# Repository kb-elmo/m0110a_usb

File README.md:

# M0110a USB
[![CC BY-NC-SA 4.0][cc-by-nc-sa-shield]][cc-by-nc-sa]

## This project is completed and will not get updated anymore.

### QMK compatible drop-in replacement PCB for the Apple M0110a
The PCB is built entirely with THT parts to keep a somewhat "vintage" look to it and it uses the fullsize 40-pin DIP package ATmega32A.
The controller is placed in the exact same location as the one on the original PCB meaning that it can be accessed through the plate cutout under the spacebar.

The board is now fully tested and works absolutely perfect. Firmware and a guide on how to flash the bootloader and firmware will be added soon.

### Partslist
 |Count|Part|
 |-|-|
 |1|ATmega32A 40 pin DIP (32L works too)|
 |1|40 pin DIP socket (optional but highly recommended)|
 |1|2x3 pin header 2.54mm (for ISP flashing)|
 |1|3mm LED (any color should work)|
 |1|JST PH 2mm 4pin connector + cable|
 |1|mini usb breakout board|
 |1|500 mA polyfuse|
 |2|6mm momentary push buttons|
 |1|16 MHz quarz crystal|
 |1|4.7 uF electrolytic capacitor|
 |2|100 nF ceramic disk capacitor|
 |2|22 pF ceramic disk capacitor|
 |1|10 kΩ resistor|
 |2|68 Ω resistor|
 |2|1.5 kΩ resistor|
 |2|3.6 V zener diode (DO-35 BZX55C3V6)|
 |78|universal switching diode (DO-35 1N4148)|

#### Some pictures of the first finished PCB

This work is licensed under a
[Creative Commons Attribution-NonCommercial-ShareAlike 4.0 International License][cc-by-nc-sa].

[![CC BY-NC-SA 4.0][cc-by-nc-sa-image]][cc-by-nc-sa]

[cc-by-nc-sa]: http://creativecommons.org/licenses/by-nc-sa/4.0/
[cc-by-nc-sa-image]: https://licensebuttons.net/l/by-nc-sa/4.0/88x31.png
[cc-by-nc-sa-shield]: https://img.shields.io/badge/License-CC%20BY--NC--SA%204.0-lightgrey.svg

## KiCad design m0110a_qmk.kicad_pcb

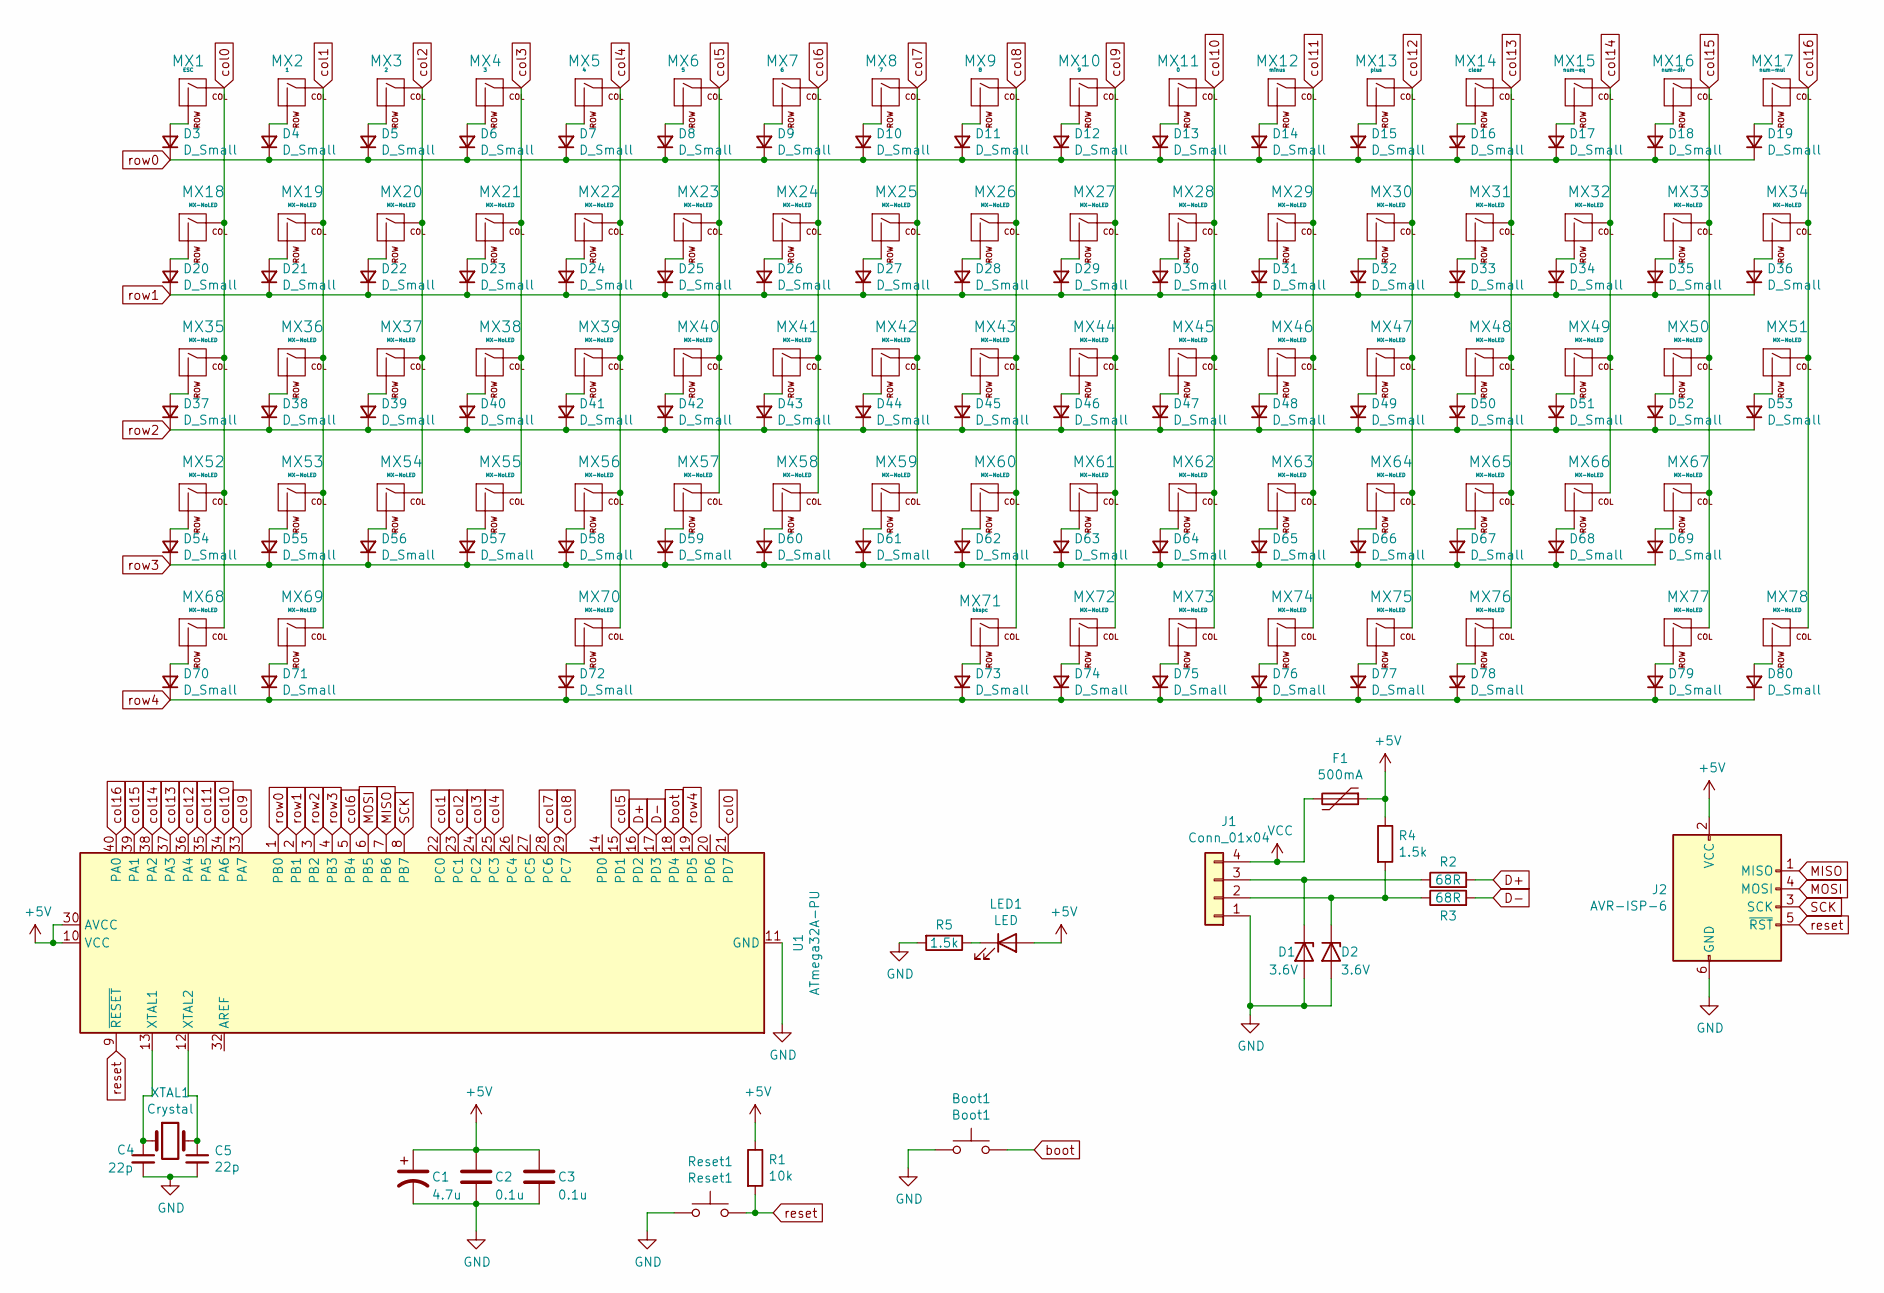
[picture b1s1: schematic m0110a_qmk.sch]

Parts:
Boot1: Boot1; SW_PUSH_6mm
C1: 4.7u; CP_Radial_D5.0mm_P2.50mm
C2, C3: 0.1u; C_Disc_D3.0mm_W2.0mm_P2.50mm
C4, C5: 22p; C_Disc_D6.0mm_W2.5mm_P5.00mm
D1, D2: 3.6V; D_DO-35_SOD27_P7.62mm_Horizontal
D3, D4, D5, D6, D7, D8, D9, D10, D11, D12, D13, D14, D15, D16, D17, D18, D19, D20, D21, D22, D23, D24, D25, D26, D27, D28, D29, D30, D31, D32, D33, D34, D35, D36, D37, D38, D39, D40, D41, D42, D43, D44, D45, D46, D47, D48, D49, D50, D51, D52, D53, D54, D55, D56, D57, D58, D59, D60, D61, D62, D63, D64, D65, D66, D67, D68, D69, D70, D71, D72, D73, D74, D75, D76, D77, D78, D79, D80: D_Small; D_DO-35_SOD27_P7.62mm_Horizontal
F1: 500mA; Fuse_Littelfuse_395Series
J1: Conn_01x04; JST_PH_S4B-PH-K_1x04_P2.00mm_Horizontal
J2: AVR-ISP-6; PinHeader_2x03_P2.54mm_Horizontal
LED1: LED; LED_D3.0mm
MX1: ESC; alps_skcc
MX2: 1; alps_skcc
MX3: 2; alps_skcc
MX4: 3; alps_skcc
MX5: 4; alps_skcc
MX6: 5; alps_skcc
MX7: 6; alps_skcc
MX8: 7; alps_skcc
MX9: 8; alps_skcc
MX10: 9; alps_skcc
MX11: 0; alps_skcc
MX12: minus; alps_skcc
MX13: plus; alps_skcc
MX14: clear; alps_skcc
MX15: num-eq; alps_skcc
MX16: num-div; alps_skcc
MX17: num-mul; alps_skcc
MX18, MX19, MX20, MX21, MX22, MX23, MX24, MX25, MX26, MX27, MX28, MX29, MX30, MX31, MX32, MX33, MX34, MX35, MX36, MX37, MX38, MX39, MX40, MX41, MX42, MX43, MX44, MX45, MX46, MX47, MX48, MX49, MX50, MX51, MX52, MX53, MX54, MX55, MX56, MX57, MX58, MX59, MX60, MX61, MX62, MX63, MX64, MX65, MX66, MX67, MX68, MX69, MX70, MX72, MX73, MX74, MX75, MX76, MX77, MX78: MX-NoLED; alps_skcc
MX71: bkspc; alps_skcc
R1: 10k; R_Axial_DIN0207_L6.3mm_D2.5mm_P10.16mm_Horizontal
R2, R3: 68R; R_Axial_DIN0207_L6.3mm_D2.5mm_P10.16mm_Horizontal
R4, R5: 1.5k; R_Axial_DIN0207_L6.3mm_D2.5mm_P10.16mm_Horizontal
Reset1: Reset1; SW_PUSH_6mm
U1: ATmega32A-PU; DIP-40_W15.24mm_Socket
XTAL1: Crystal; Crystal_HC49-4H_Vertical

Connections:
+5V: C1.1, C2.1, C3.1, F1.1, J2.2 (VCC), LED1.2 (A), R1.1, R4.1, U1.10 (VCC), U1.30 (AVCC)
D+: R2.2, U1.16 (PD2)
D-: R3.2, U1.17 (PD3)
GND: Boot1.1, C1.2, C2.2, C3.2, C4.2, C5.2, D1.2 (A), D2.2 (A), J1.1, J2.6 (GND), R5.2, Reset1.1, U1.11 (GND), U1.31 (GND)
MISO: J2.1 (MISO), U1.7 (PB6)
MOSI: J2.4 (MOSI), U1.6 (PB5)
unnamed: C4.1, U1.13 (XTAL1), XTAL1.1
unnamed: C5.1, U1.12 (XTAL2), XTAL1.2
unnamed: D1.1 (K), J1.3, R2.1
unnamed: D2.1 (K), J1.2, R3.1, R4.2
unnamed: D3.2 (A), MX1.2 (ROW)
unnamed: D4.2 (A), MX2.2 (ROW)
unnamed: D5.2 (A), MX3.2 (ROW)
unnamed: D6.2 (A), MX4.2 (ROW)
unnamed: D7.2 (A), MX5.2 (ROW)
unnamed: D8.2 (A), MX6.2 (ROW)
unnamed: D9.2 (A), MX7.2 (ROW)
unnamed: D10.2 (A), MX8.2 (ROW)
unnamed: D11.2 (A), MX9.2 (ROW)
unnamed: D12.2 (A), MX10.2 (ROW)
unnamed: D13.2 (A), MX11.2 (ROW)
unnamed: D14.2 (A), MX12.2 (ROW)
unnamed: D15.2 (A), MX13.2 (ROW)
unnamed: D16.2 (A), MX14.2 (ROW)
unnamed: D17.2 (A), MX15.2 (ROW)
unnamed: D18.2 (A), MX16.2 (ROW)
unnamed: D19.2 (A), MX17.2 (ROW)
unnamed: D20.2 (A), MX18.2 (ROW)
unnamed: D21.2 (A), MX19.2 (ROW)
unnamed: D22.2 (A), MX20.2 (ROW)
unnamed: D23.2 (A), MX21.2 (ROW)
unnamed: D24.2 (A), MX22.2 (ROW)
unnamed: D25.2 (A), MX23.2 (ROW)
unnamed: D26.2 (A), MX24.2 (ROW)
unnamed: D27.2 (A), MX25.2 (ROW)
unnamed: D28.2 (A), MX26.2 (ROW)
unnamed: D29.2 (A), MX27.2 (ROW)
unnamed: D30.2 (A), MX28.2 (ROW)
unnamed: D31.2 (A), MX29.2 (ROW)
unnamed: D32.2 (A), MX30.2 (ROW)
unnamed: D33.2 (A), MX31.2 (ROW)
unnamed: D34.2 (A), MX32.2 (ROW)
unnamed: D35.2 (A), MX33.2 (ROW)
unnamed: D36.2 (A), MX34.2 (ROW)
unnamed: D37.2 (A), MX35.2 (ROW)
unnamed: D38.2 (A), MX36.2 (ROW)
unnamed: D39.2 (A), MX37.2 (ROW)
unnamed: D40.2 (A), MX38.2 (ROW)
unnamed: D41.2 (A), MX39.2 (ROW)
unnamed: D42.2 (A), MX40.2 (ROW)
unnamed: D43.2 (A), MX41.2 (ROW)
unnamed: D44.2 (A), MX42.2 (ROW)
unnamed: D45.2 (A), MX43.2 (ROW)
unnamed: D46.2 (A), MX44.2 (ROW)
unnamed: D47.2 (A), MX45.2 (ROW)
unnamed: D48.2 (A), MX46.2 (ROW)
unnamed: D49.2 (A), MX47.2 (ROW)
unnamed: D50.2 (A), MX48.2 (ROW)
unnamed: D51.2 (A), MX49.2 (ROW)
unnamed: D52.2 (A), MX50.2 (ROW)
unnamed: D53.2 (A), MX51.2 (ROW)
unnamed: D54.2 (A), MX52.2 (ROW)
unnamed: D55.2 (A), MX53.2 (ROW)
unnamed: D56.2 (A), MX54.2 (ROW)
unnamed: D57.2 (A), MX55.2 (ROW)
unnamed: D58.2 (A), MX56.2 (ROW)
unnamed: D59.2 (A), MX57.2 (ROW)
unnamed: D60.2 (A), MX58.2 (ROW)
unnamed: D61.2 (A), MX59.2 (ROW)
unnamed: D62.2 (A), MX60.2 (ROW)
unnamed: D63.2 (A), MX61.2 (ROW)
unnamed: D64.2 (A), MX62.2 (ROW)
unnamed: D65.2 (A), MX63.2 (ROW)
unnamed: D66.2 (A), MX64.2 (ROW)
unnamed: D67.2 (A), MX65.2 (ROW)
unnamed: D68.2 (A), MX66.2 (ROW)
unnamed: D69.2 (A), MX67.2 (ROW)
unnamed: D70.2 (A), MX68.2 (ROW)
unnamed: D71.2 (A), MX69.2 (ROW)
unnamed: D72.2 (A), MX70.2 (ROW)
unnamed: D73.2 (A), MX71.2 (ROW)
unnamed: D74.2 (A), MX72.2 (ROW)
unnamed: D75.2 (A), MX73.2 (ROW)
unnamed: D76.2 (A), MX74.2 (ROW)
unnamed: D77.2 (A), MX75.2 (ROW)
unnamed: D78.2 (A), MX76.2 (ROW)
unnamed: D79.2 (A), MX77.2 (ROW)
unnamed: D80.2 (A), MX78.2 (ROW)
unnamed: LED1.1 (K), R5.1
SCK: J2.3 (SCK), U1.8 (PB7)
VCC: F1.2, J1.4
boot: Boot1.2, U1.18 (PD4)
col0: MX1.1 (COL), MX18.1 (COL), MX35.1 (COL), MX52.1 (COL), MX68.1 (COL), U1.21 (PD7)
col1: MX2.1 (COL), MX19.1 (COL), MX36.1 (COL), MX53.1 (COL), MX69.1 (COL), U1.22 (PC0)
col2: MX3.1 (COL), MX20.1 (COL), MX37.1 (COL), MX54.1 (COL), U1.23 (PC1)
col3: MX4.1 (COL), MX21.1 (COL), MX38.1 (COL), MX55.1 (COL), U1.24 (PC2)
col4: MX5.1 (COL), MX22.1 (COL), MX39.1 (COL), MX56.1 (COL), MX70.1 (COL), U1.25 (PC3)
col5: MX6.1 (COL), MX23.1 (COL), MX40.1 (COL), MX57.1 (COL), U1.15 (PD1)
col6: MX7.1 (COL), MX24.1 (COL), MX41.1 (COL), MX58.1 (COL), U1.5 (PB4)
col7: MX8.1 (COL), MX25.1 (COL), MX42.1 (COL), MX59.1 (COL), U1.28 (PC6)
col8: MX9.1 (COL), MX26.1 (COL), MX43.1 (COL), MX60.1 (COL), MX71.1 (COL), U1.29 (PC7)
col9: MX10.1 (COL), MX27.1 (COL), MX44.1 (COL), MX61.1 (COL), MX72.1 (COL), U1.33 (PA7)
col10: MX11.1 (COL), MX28.1 (COL), MX45.1 (COL), MX62.1 (COL), MX73.1 (COL), U1.34 (PA6)
col11: MX12.1 (COL), MX29.1 (COL), MX46.1 (COL), MX63.1 (COL), MX74.1 (COL), U1.35 (PA5)
col12: MX13.1 (COL), MX30.1 (COL), MX47.1 (COL), MX64.1 (COL), MX75.1 (COL), U1.36 (PA4)
col13: MX14.1 (COL), MX31.1 (COL), MX48.1 (COL), MX65.1 (COL), MX76.1 (COL), U1.37 (PA3)
col14: MX15.1 (COL), MX32.1 (COL), MX49.1 (COL), MX66.1 (COL), U1.38 (PA2)
col15: MX16.1 (COL), MX33.1 (COL), MX50.1 (COL), MX67.1 (COL), MX77.1 (COL), U1.39 (PA1)
col16: MX17.1 (COL), MX34.1 (COL), MX51.1 (COL), MX78.1 (COL), U1.40 (PA0)
reset: J2.5 (~RST), R1.2, Reset1.2, U1.9 (~RESET)
row0: D3.1 (K), D4.1 (K), D5.1 (K), D6.1 (K), D7.1 (K), D8.1 (K), D9.1 (K), D10.1 (K), D11.1 (K), D12.1 (K), D13.1 (K), D14.1 (K), D15.1 (K), D16.1 (K), D17.1 (K), D18.1 (K), D19.1 (K), U1.1 (PB0)
row1: D20.1 (K), D21.1 (K), D22.1 (K), D23.1 (K), D24.1 (K), D25.1 (K), D26.1 (K), D27.1 (K), D28.1 (K), D29.1 (K), D30.1 (K), D31.1 (K), D32.1 (K), D33.1 (K), D34.1 (K), D35.1 (K), D36.1 (K), U1.2 (PB1)
row2: D37.1 (K), D38.1 (K), D39.1 (K), D40.1 (K), D41.1 (K), D42.1 (K), D43.1 (K), D44.1 (K), D45.1 (K), D46.1 (K), D47.1 (K), D48.1 (K), D49.1 (K), D50.1 (K), D51.1 (K), D52.1 (K), D53.1 (K), U1.3 (PB2)
row3: D54.1 (K), D55.1 (K), D56.1 (K), D57.1 (K), D58.1 (K), D59.1 (K), D60.1 (K), D61.1 (K), D62.1 (K), D63.1 (K), D64.1 (K), D65.1 (K), D66.1 (K), D67.1 (K), D68.1 (K), D69.1 (K), U1.4 (PB3)
row4: D70.1 (K), D71.1 (K), D72.1 (K), D73.1 (K), D74.1 (K), D75.1 (K), D76.1 (K), D77.1 (K), D78.1 (K), D79.1 (K), D80.1 (K), U1.19 (PD5)

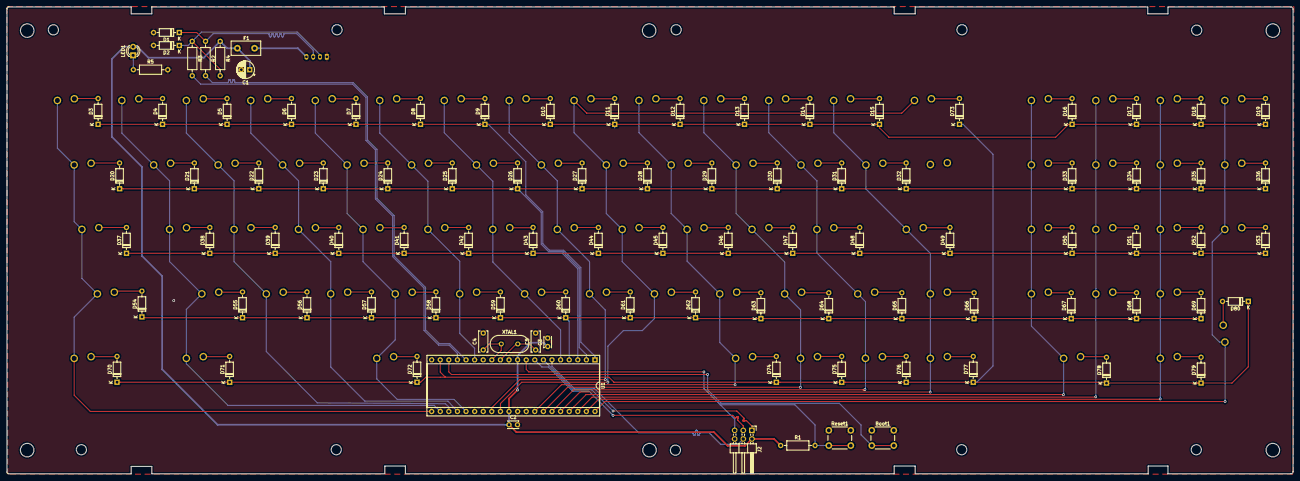
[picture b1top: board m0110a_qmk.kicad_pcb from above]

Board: 2 copper layers, 380.0 x 137.9 mm, 177 parts (1 on the bottom side), 115 nets.

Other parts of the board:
MX80: MX-NoLED; alps_skcc

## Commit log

2020-05-17 Initial commit
    created KiCad Project
2020-05-17 added submodules
2020-05-17 add libraries
2020-05-17 basic controller setup
2020-05-17 some changes to the controller circuit
2020-05-17 finished circuit schema
2020-05-17 finish footprint matching
2020-05-18 finished pcb layout
2020-05-18 finish pcb
2020-05-18 fixed USB port orientation
2020-05-18 flipped diodes and added groundplanes
2020-05-18 changed footprints
2020-05-18 removed unnecessary vias
2020-05-18 small update
2020-05-18 cosmetic stuff
2020-05-18 change logos
2020-05-18 more logos!
    now in copper :)
2020-05-18 fixed logos
2020-05-18 some trace changes
2020-05-18 fix screw-hole positions and generate gerbers
2020-05-20 fixes for newer keycad versions
    fixed pathes for 3d parts
2020-05-28 fix some mistakes
2020-06-03 rev1
2020-06-04 change JST connector size
2020-06-04 update gerbers
2020-06-10 QMK stuff
2020-06-10 update qmk readme
2020-06-10 add USBasp bootloader files
2020-06-17 add guide
2020-06-20 update guide
2020-07-11 Update LICENSE
